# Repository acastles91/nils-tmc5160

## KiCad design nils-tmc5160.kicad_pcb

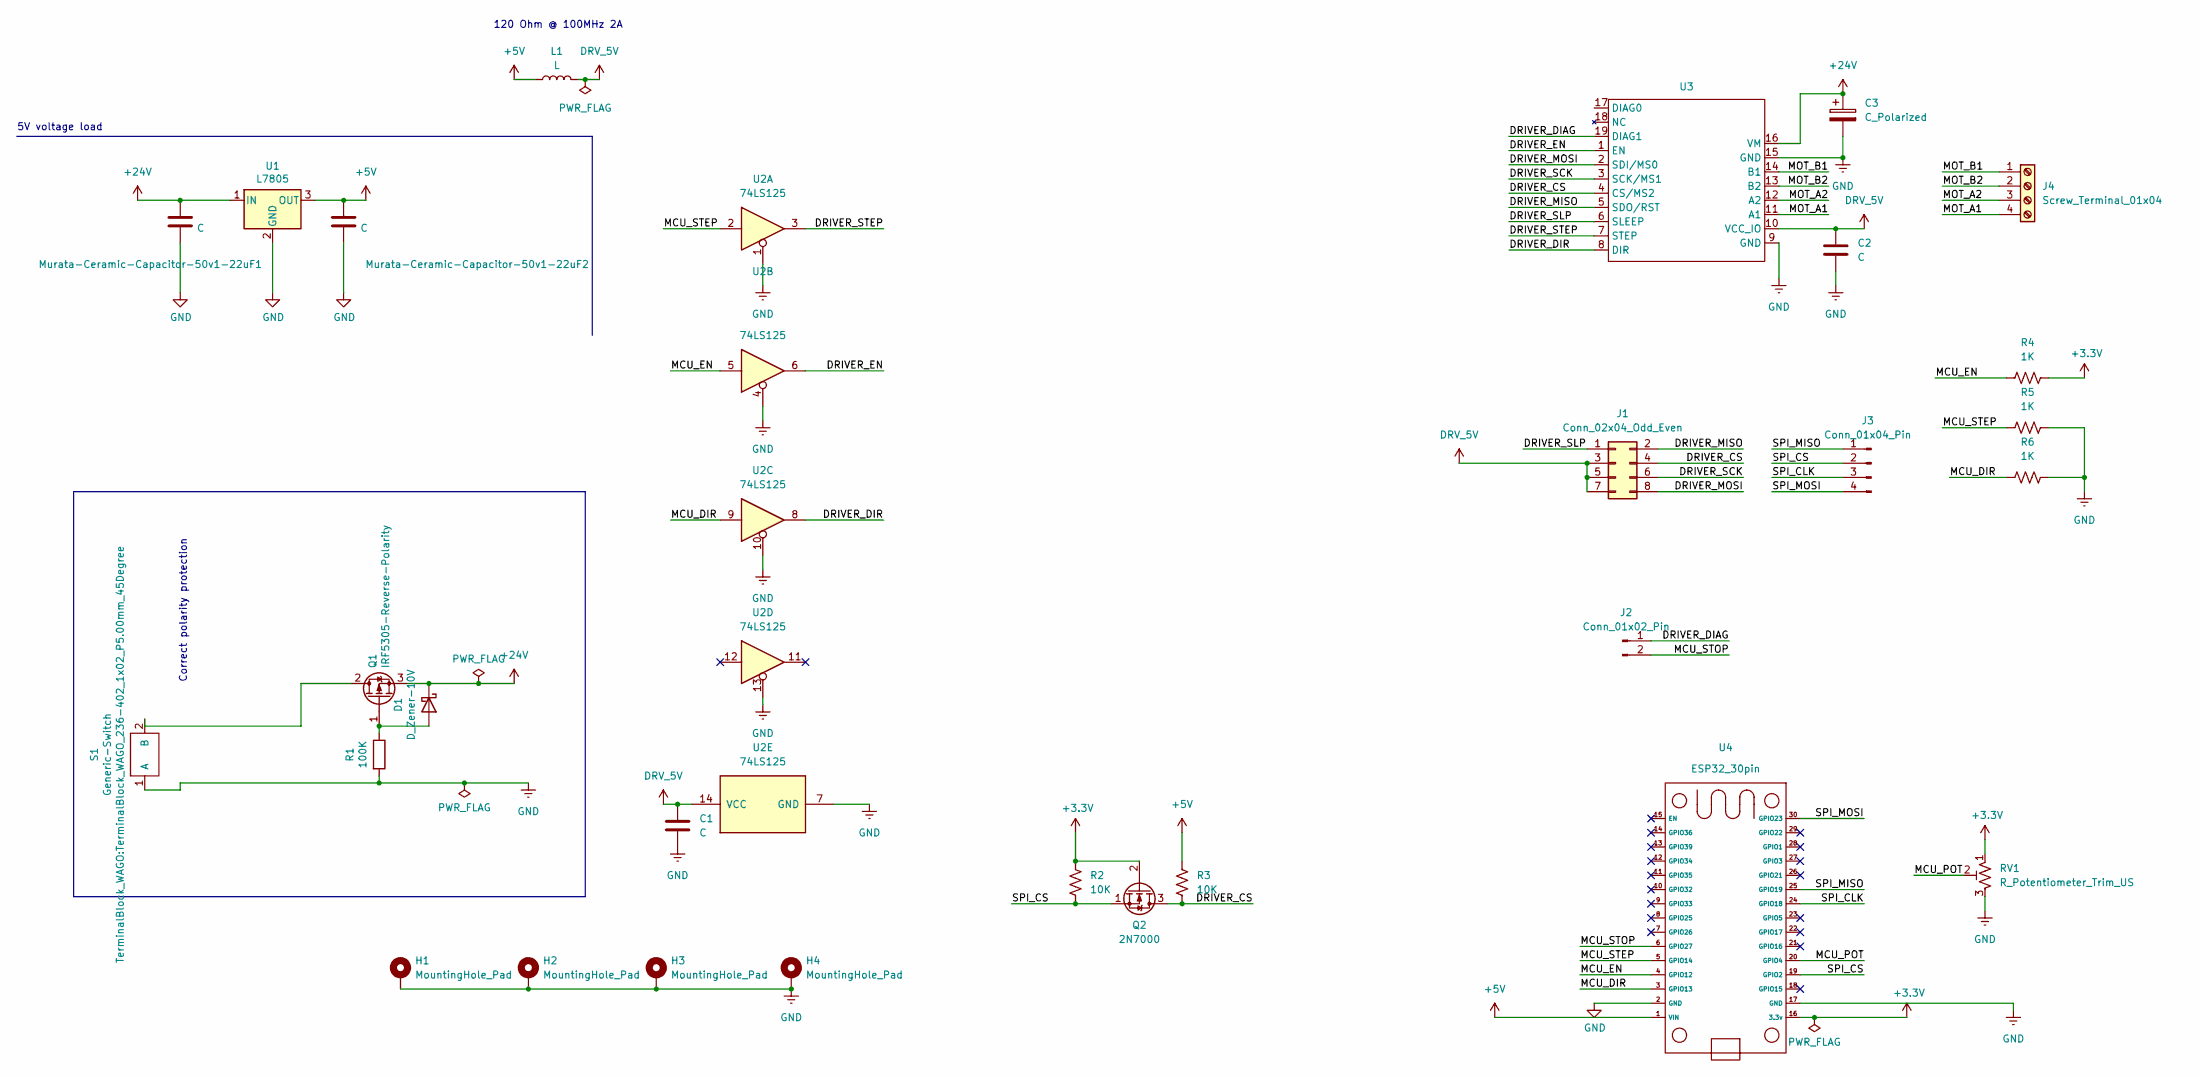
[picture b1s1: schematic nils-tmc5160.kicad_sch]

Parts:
C1, C2: C; C_Disc_D5.0mm_W2.5mm_P2.50mm
C3: C_Polarized; CP_Radial_D8.0mm_P5.00mm
D1: D_Zener-10V; D_DO-41_SOD81_P7.62mm_Horizontal
H1, H2, H3, H4: MountingHole_Pad; MountingHole_3.2mm_M3_Pad_Via
J1: Conn_02x04_Odd_Even; PinHeader_2x04_P2.54mm_Vertical
J2: Conn_01x02_Pin; PinHeader_1x02_P2.54mm_Vertical
J3: Conn_01x04_Pin; PinHeader_1x04_P2.54mm_Vertical
J4: Screw_Terminal_01x04; TerminalBlock_WAGO_236-404_1x04_P5.00mm_45Degree
L1: L; R_Axial_DIN0204_L3.6mm_D1.6mm_P7.62mm_Horizontal
Murata-Ceramic-Capacitor-50v1-22uF1, Murata-Ceramic-Capacitor-50v1-22uF2: C; C_Disc_D3.0mm_W1.6mm_P2.50mm
Q1: IRF5305-Reverse-Polarity; TO-220-3_Horizontal_TabDown
Q2: 2N7000; TO-92_Inline
R1: 100K; R_Axial_DIN0204_L3.6mm_D1.6mm_P7.62mm_Horizontal
R2, R3: 10K; R_Axial_DIN0204_L3.6mm_D1.6mm_P7.62mm_Horizontal
R4, R5, R6: 1K; R_Axial_DIN0204_L3.6mm_D1.6mm_P7.62mm_Horizontal
RV1: R_Potentiometer_Trim_US; Potentiometer_Bourns_3296W_Vertical
S1: Generic-Switch; TerminalBlock_WAGO_236-402_1x02_P5.00mm_45Degree
U1: L7805; TO-220-3_Horizontal_TabDown
U2: 74LS125; DIP-14_W7.62mm
U3: MODULE_TMC5160_SILENTSTEPSTICK
U4: ESP32_30pin

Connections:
+3.3V: Q2.2 (G), R2.2, R4.2, RV1.1, U4.16 (3.3v)
+5V: L1.1, Murata-Ceramic-Capacitor-50v1-22uF2.1, R3.2, U1.3 (OUT), U4.1 (VIN)
+24V: C3.1, D1.1 (K), Murata-Ceramic-Capacitor-50v1-22uF1.1, Q1.3 (S), U1.1 (IN), U3.16 (VM)
/DRIVER_CS: J1.4, Q2.3 (D), R3.1, U3.4 (CS/MS2)
/DRIVER_DIAG: J2.1, U3.19 (DIAG1)
/DRIVER_DIR: U2.8, U3.8 (DIR)
/DRIVER_EN: U2.6, U3.1 (EN)
/DRIVER_MISO: J1.2, U3.5 (SDO/RST)
/DRIVER_MOSI: J1.8, U3.2 (SDI/MS0)
/DRIVER_SCK: J1.6, U3.3 (SCK/MS1)
/DRIVER_SLP: J1.1, U3.6 (SLEEP)
/DRIVER_STEP: U2.3, U3.7 (STEP)
/MCU_DIR: R6.1, U2.9, U4.3 (GPIO13)
/MCU_EN: R4.1, U2.5, U4.4 (GPIO12)
/MCU_POT: RV1.2, U4.20 (GPIO4)
/MCU_STEP: R5.1, U2.2, U4.5 (GPIO14)
/MCU_STOP: J2.2, U4.6 (GPIO27)
/MOT_A1: J4.4, U3.11 (A1)
/MOT_A2: J4.3, U3.12 (A2)
/MOT_B1: J4.1, U3.14 (B1)
/MOT_B2: J4.2, U3.13 (B2)
/SPI_CLK: J3.3, U4.24 (GPIO18)
/SPI_CS: J3.2, Q2.1 (S), R2.1, U4.19 (GPIO2)
/SPI_MISO: J3.1, U4.25 (GPIO19)
/SPI_MOSI: J3.4, U4.30 (GPIO23)
DRV_5V: C1.1, C2.1, J1.3, J1.5, J1.7, L1.2, U2.14 (VCC), U3.10 (VCC_IO)
GND: C1.2, C2.2, C3.2, H1.1, H2.1, H3.1, H4.1, Murata-Ceramic-Capacitor-50v1-22uF1.2, Murata-Ceramic-Capacitor-50v1-22uF2.2, R1.2, R5.2, R6.2, RV1.3, S1.1 (A), U1.2 (GND), U2.1, U2.4, U2.7 (GND), U2.10, U2.13, U3.9 (GND), U3.15 (GND), U4.2 (GND), U4.17 (GND)
unnamed: D1.2 (A), Q1.1 (G), R1.1
unnamed: Q1.2 (D), S1.2 (B)

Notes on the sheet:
5V voltage load
Correct polarity protection
120 Ohm @ 100MHz 2A

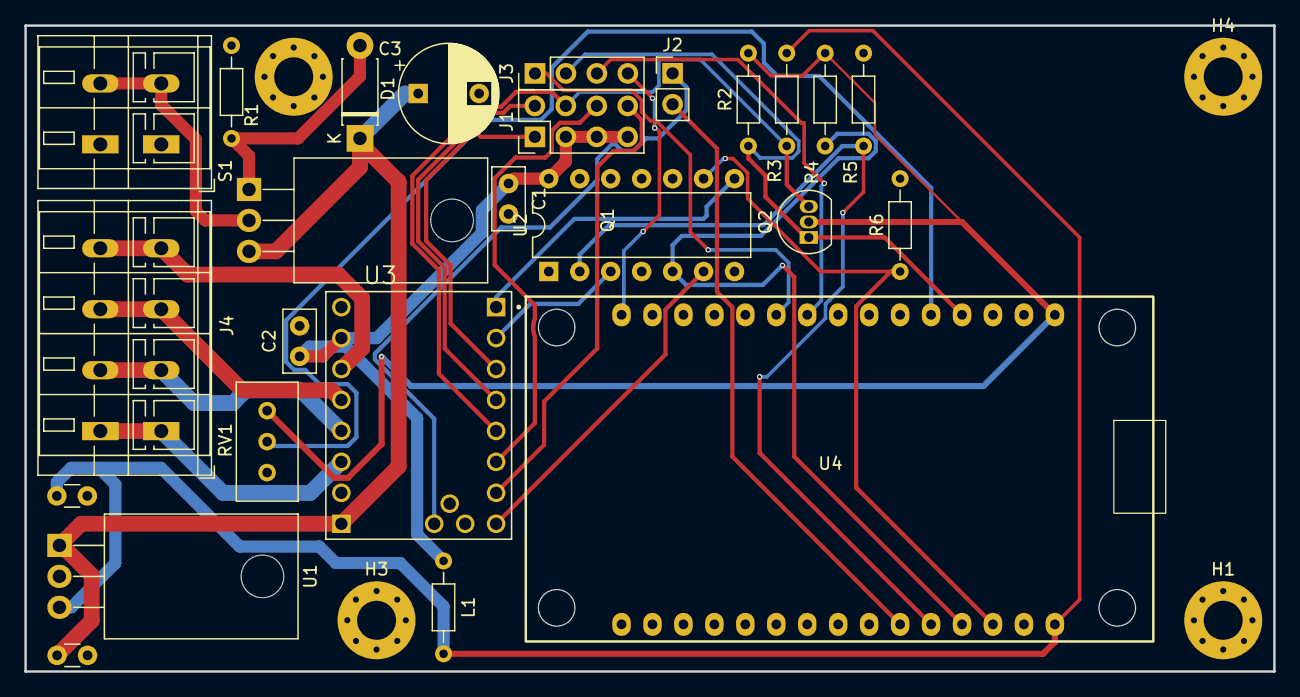
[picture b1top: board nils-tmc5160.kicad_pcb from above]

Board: 4 copper layers, 102.5 x 53.0 mm, 29 parts (0 on the bottom side), 29 nets.

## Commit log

2025-06-30 added rev1 of hardware to the repository
